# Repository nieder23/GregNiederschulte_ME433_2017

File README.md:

Greg Niederschulte
March 29, 2017

This repository is the collection of my work for the class ME 433 at Northwestern University, called Advanced Mechatronics. The class has us complete various projects to teach the skills involved in mechatronics design and programming. We wrap up the quarter with a project of a robotic cart that can follow a line on a course using a programmed Android device.

This course is not required but serves as a strong educational basis for further mechatronics/robotics projects, which I am highly interested in exploring.

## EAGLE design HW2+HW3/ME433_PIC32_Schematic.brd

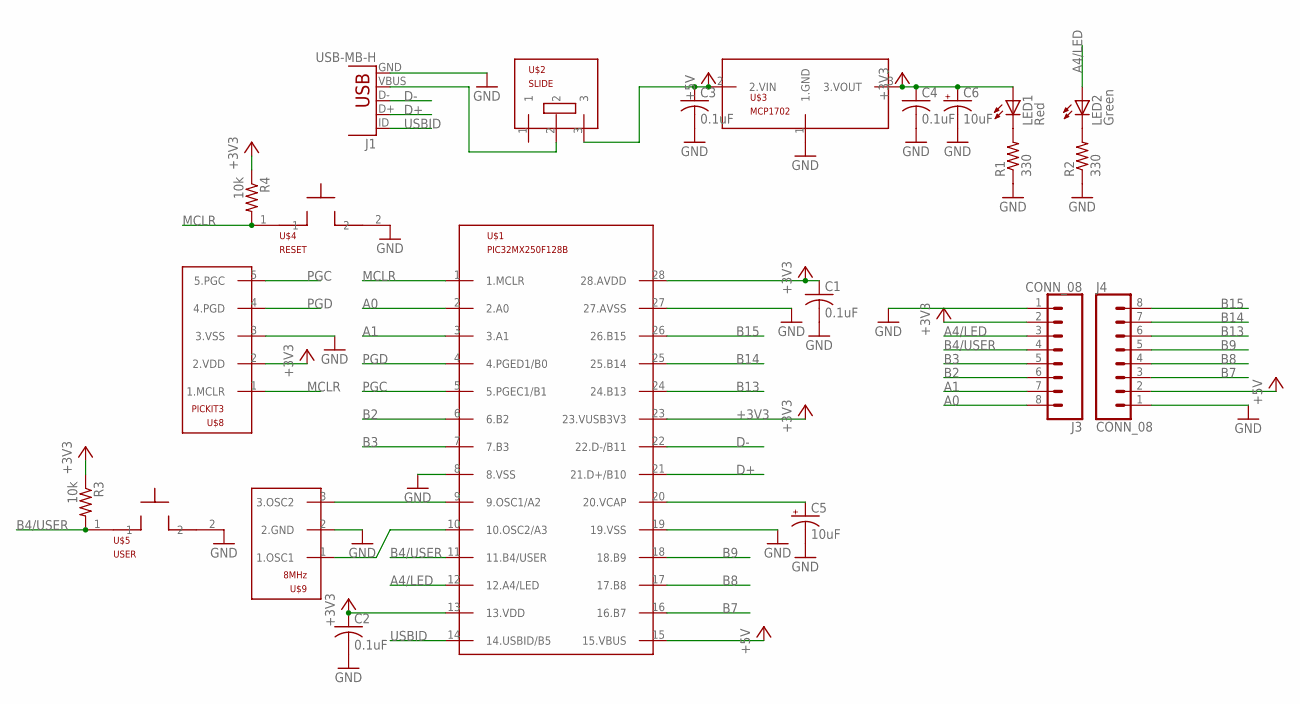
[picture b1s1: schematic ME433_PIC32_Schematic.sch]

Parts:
C1, C2, C3, C4: 0.1uF; C025-025X050
C5, C6: 10uF; B45181B
J1: USB-MB-H
J3, J4: CONN_08; 1X08
LED1: Red; LED3MM
LED2: Green; LED3MM
R1, R2: 330; 0207/10
R3, R4: 10k; 0207/10
U$1: PIC32MX250F128B; DIL28-3
U$2: SLIDE
U$3: MCP1702; TO92
U$4: RESET; PB
U$5: USER; PB
U$8: PICKIT3; 1X05
U$9: 8MHz; OSC

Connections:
+3V3: C1.1, C2.1, C4.1, C6.+, J3.2, LED1.A, R3.1, R4.1, U$1.13 (13.VDD), U$1.23 (23.VUSB3V3), U$1.28 (28.AVDD), U$3.3 (3.VOUT), U$8.2 (2.VDD)
+5V: C3.1, J4.2, U$1.15 (15.VBUS), U$2.3, U$3.2 (2.VIN)
A0: J3.8, U$1.2 (2.A0)
A1: J3.7, U$1.3 (3.A1)
A4/LED: J3.3, LED2.A, U$1.12 (12.A4/LED)
B2: J3.6, U$1.6 (6.B2)
B3: J3.5, U$1.7 (7.B3)
B4/USER: J3.4, R3.2, U$1.11 (11.B4/USER), U$5.1
B7: J4.3, U$1.16 (16.B7)
B8: J4.4, U$1.17 (17.B8)
B9: J4.5, U$1.18 (18.B9)
B13: J4.6, U$1.24 (24.B13)
B14: J4.7, U$1.25 (25.B14)
B15: J4.8, U$1.26 (26.B15)
D+: J1.D+, U$1.21 (21.D+/B10)
D-: J1.D-, U$1.22 (22.D-/B11)
GND: C1.2, C2.2, C3.2, C4.2, C5.-, C6.-, J1.GND, J3.1, J4.1, R1.1, R2.1, U$1.8 (8.VSS), U$1.19 (19.VSS), U$1.27 (27.AVSS), U$3.1 (1.GND), U$4.2, U$5.2, U$8.3 (3.VSS), U$9.2 (2.GND)
MCLR: R4.2, U$1.1 (1.MCLR), U$4.1, U$8.1 (1.MCLR)
unnamed: J1.VBUS, U$2.2
unnamed: U$1.9 (9.OSC1/A2), U$9.3 (3.OSC2)
unnamed: LED1.K (C), R1.2
unnamed: U$1.10 (10.OSC2/A3), U$9.1 (1.OSC1)
unnamed: C5.+, U$1.20 (20.VCAP)
unnamed: LED2.K (C), R2.2
PGC: U$1.5 (5.PGEC1/B1), U$8.5 (5.PGC)
PGD: U$1.4 (4.PGED1/B0), U$8.4 (4.PGD)
USBID: J1.ID, U$1.14 (14.USBID/B5)

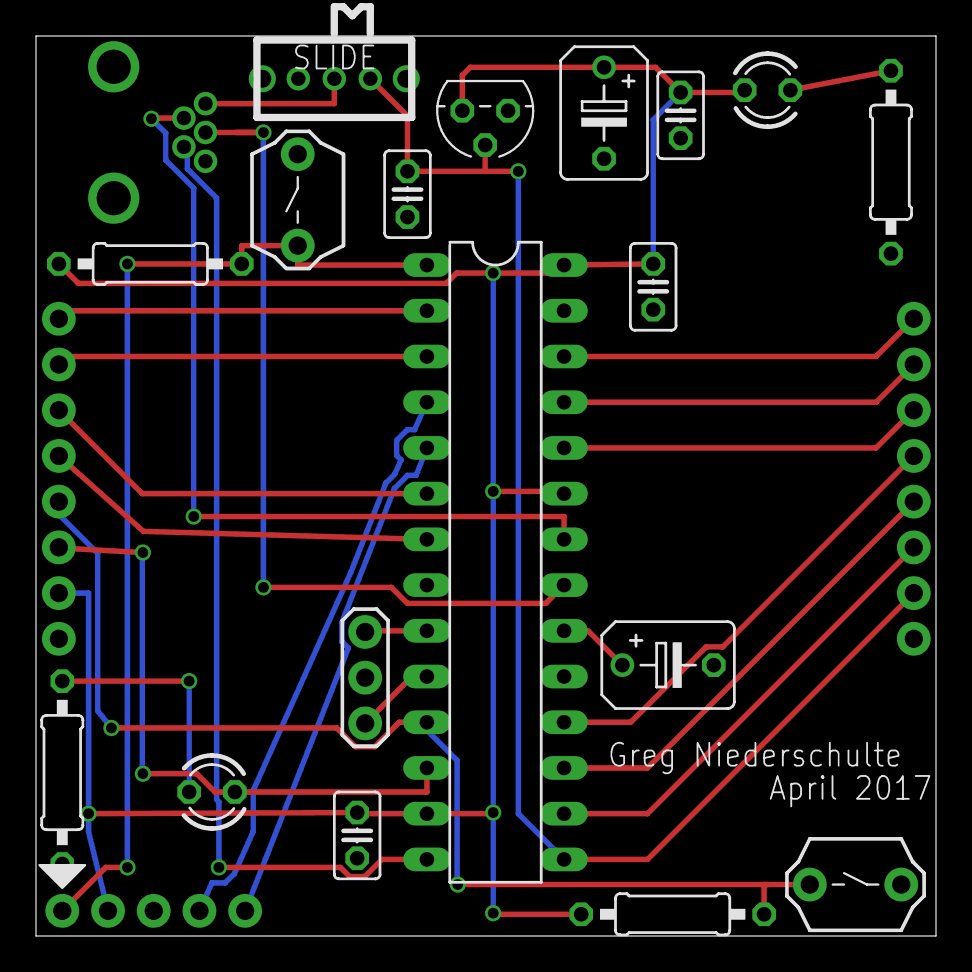
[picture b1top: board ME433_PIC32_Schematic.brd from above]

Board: 2 copper layers, 50.0 x 50.0 mm, 22 parts (0 on the bottom side), 27 nets.

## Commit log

2017-03-30 My First Commit!
2017-03-30 My Second Commit!
2017-03-30 2.1 Voltage Regulator Fuzzy Voltage
2017-03-30 Clean Voltage Screenshot
2017-04-01 Created the MPlab HW1 Project
2017-04-02 Configured all Pragma parameters
2017-04-03 Adjustments to main.c
2017-04-03 Circuit Diagram of HW1
2017-04-03 Breadboard Photos
2017-04-05 Coding the PIC changes
2017-04-06 Cleaned up files
2017-04-07 Correct Code (verified it works) and the remainder of HW1 assignment
2017-04-07 HW1 Video
2017-04-07 Eagle Project Upload
2017-04-07 Eagle Work
2017-04-07 More Eagle Changes
2017-04-14 Created Gerber Files, Ready For Order
2017-04-17 Revision
2017-05-10 Homework 12
2017-05-24 HW13
2017-06-07 Made changes to the java
2017-06-08 Finalized app for image analysis
2017-06-08 Got HW8 Working
2017-06-08 Got CDC Communication working
2018-06-13 Cleaned up some files
2018-06-18 HW4 Completed
2018-06-18 HW15
2018-06-18 HW17
2018-06-18 HW20
2018-06-18 HW16
2018-06-18 HW18
2018-06-18 HW20 Video
2018-06-18 HW17 Video
2018-06-18 HW 19
